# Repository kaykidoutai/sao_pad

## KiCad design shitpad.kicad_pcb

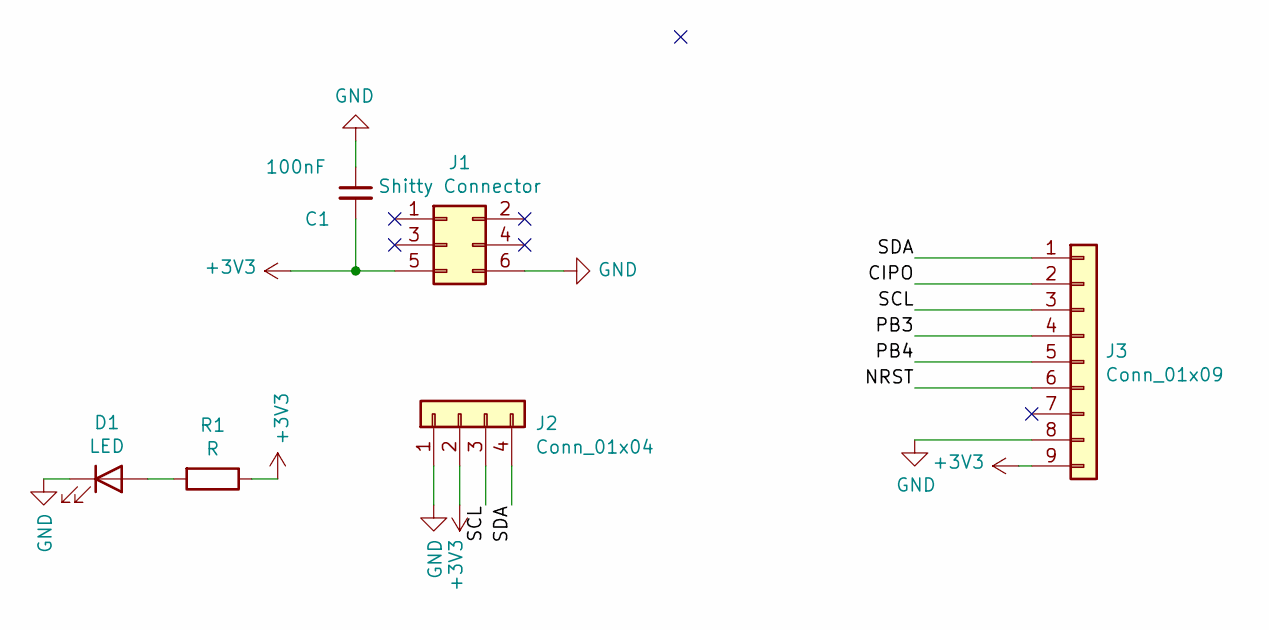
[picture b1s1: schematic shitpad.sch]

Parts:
C1: 100nF; C_0805_2012Metric_Pad1.18x1.45mm_HandSolder
D1: LED; LED_D3.0mm
J1: Shitty Connector; PinSocket_2x03_P2.54mm_Vertical_SMD
J2: Conn_01x04; OLED_I2C
J3: Conn_01x09; Digispark
R1: R; R_Axial_DIN0207_L6.3mm_D2.5mm_P10.16mm_Horizontal

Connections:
+3V3: C1.2, J1.5, J2.2, J3.9, R1.1
/CIPO: J3.2
/NRST: J3.6
/PB3: J3.4
/PB4: J3.5
/SCL: J2.3, J3.3
/SDA: J2.4, J3.1
GND: C1.1, D1.1 (K), J1.6, J2.1, J3.8
unnamed: D1.2 (A), R1.2

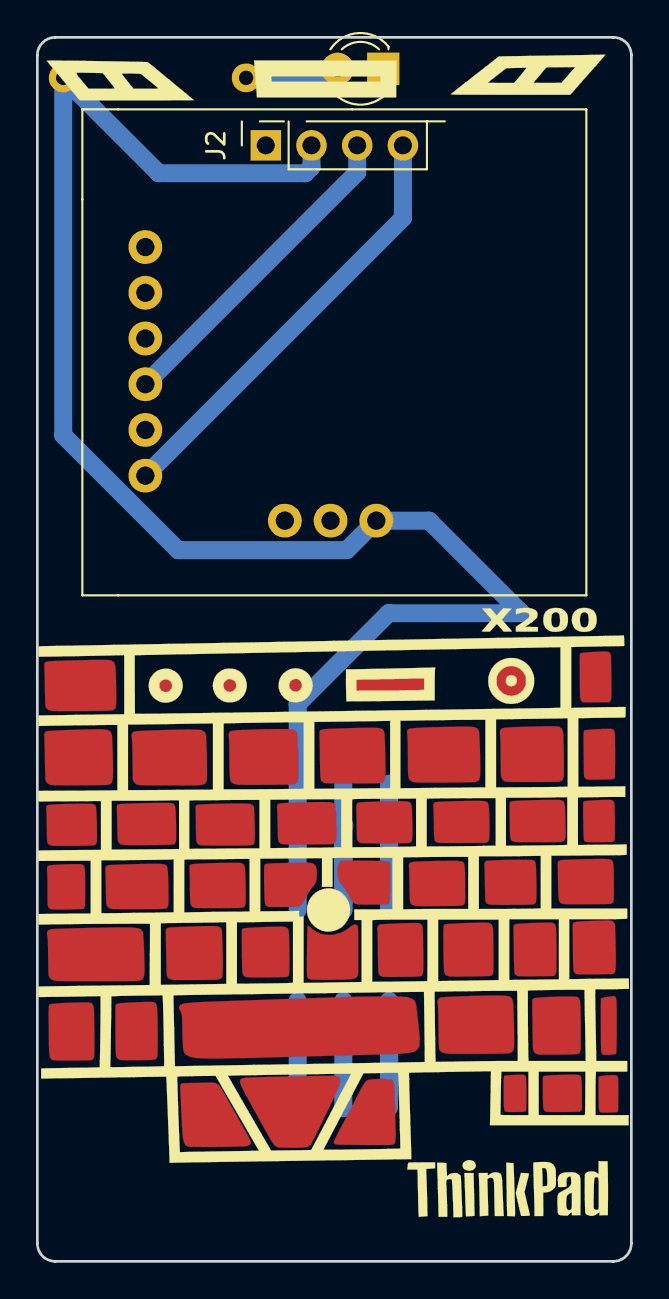
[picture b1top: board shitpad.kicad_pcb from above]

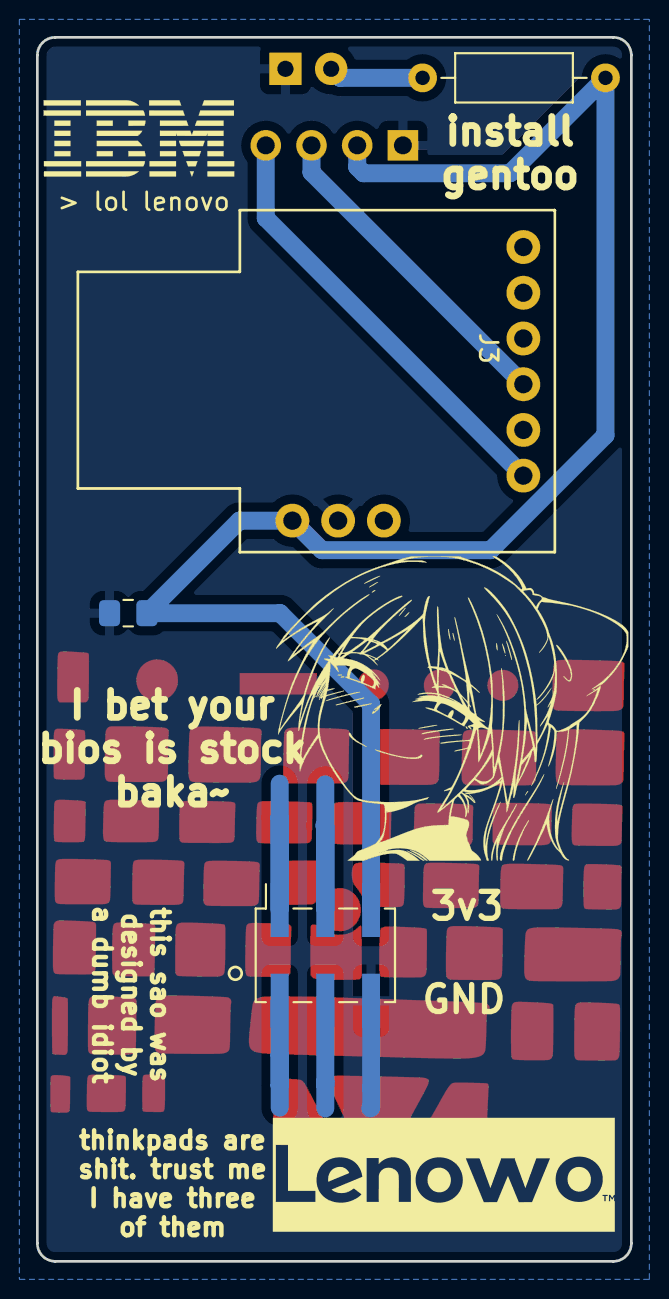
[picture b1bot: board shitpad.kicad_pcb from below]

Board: 2 copper layers, 33.0 x 68.0 mm, 6 parts (4 on the bottom side), 5 nets.

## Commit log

2022-07-04 it's shit
2022-10-09 round 2
2022-11-24 ordered
2023-07-27 did some stuff
